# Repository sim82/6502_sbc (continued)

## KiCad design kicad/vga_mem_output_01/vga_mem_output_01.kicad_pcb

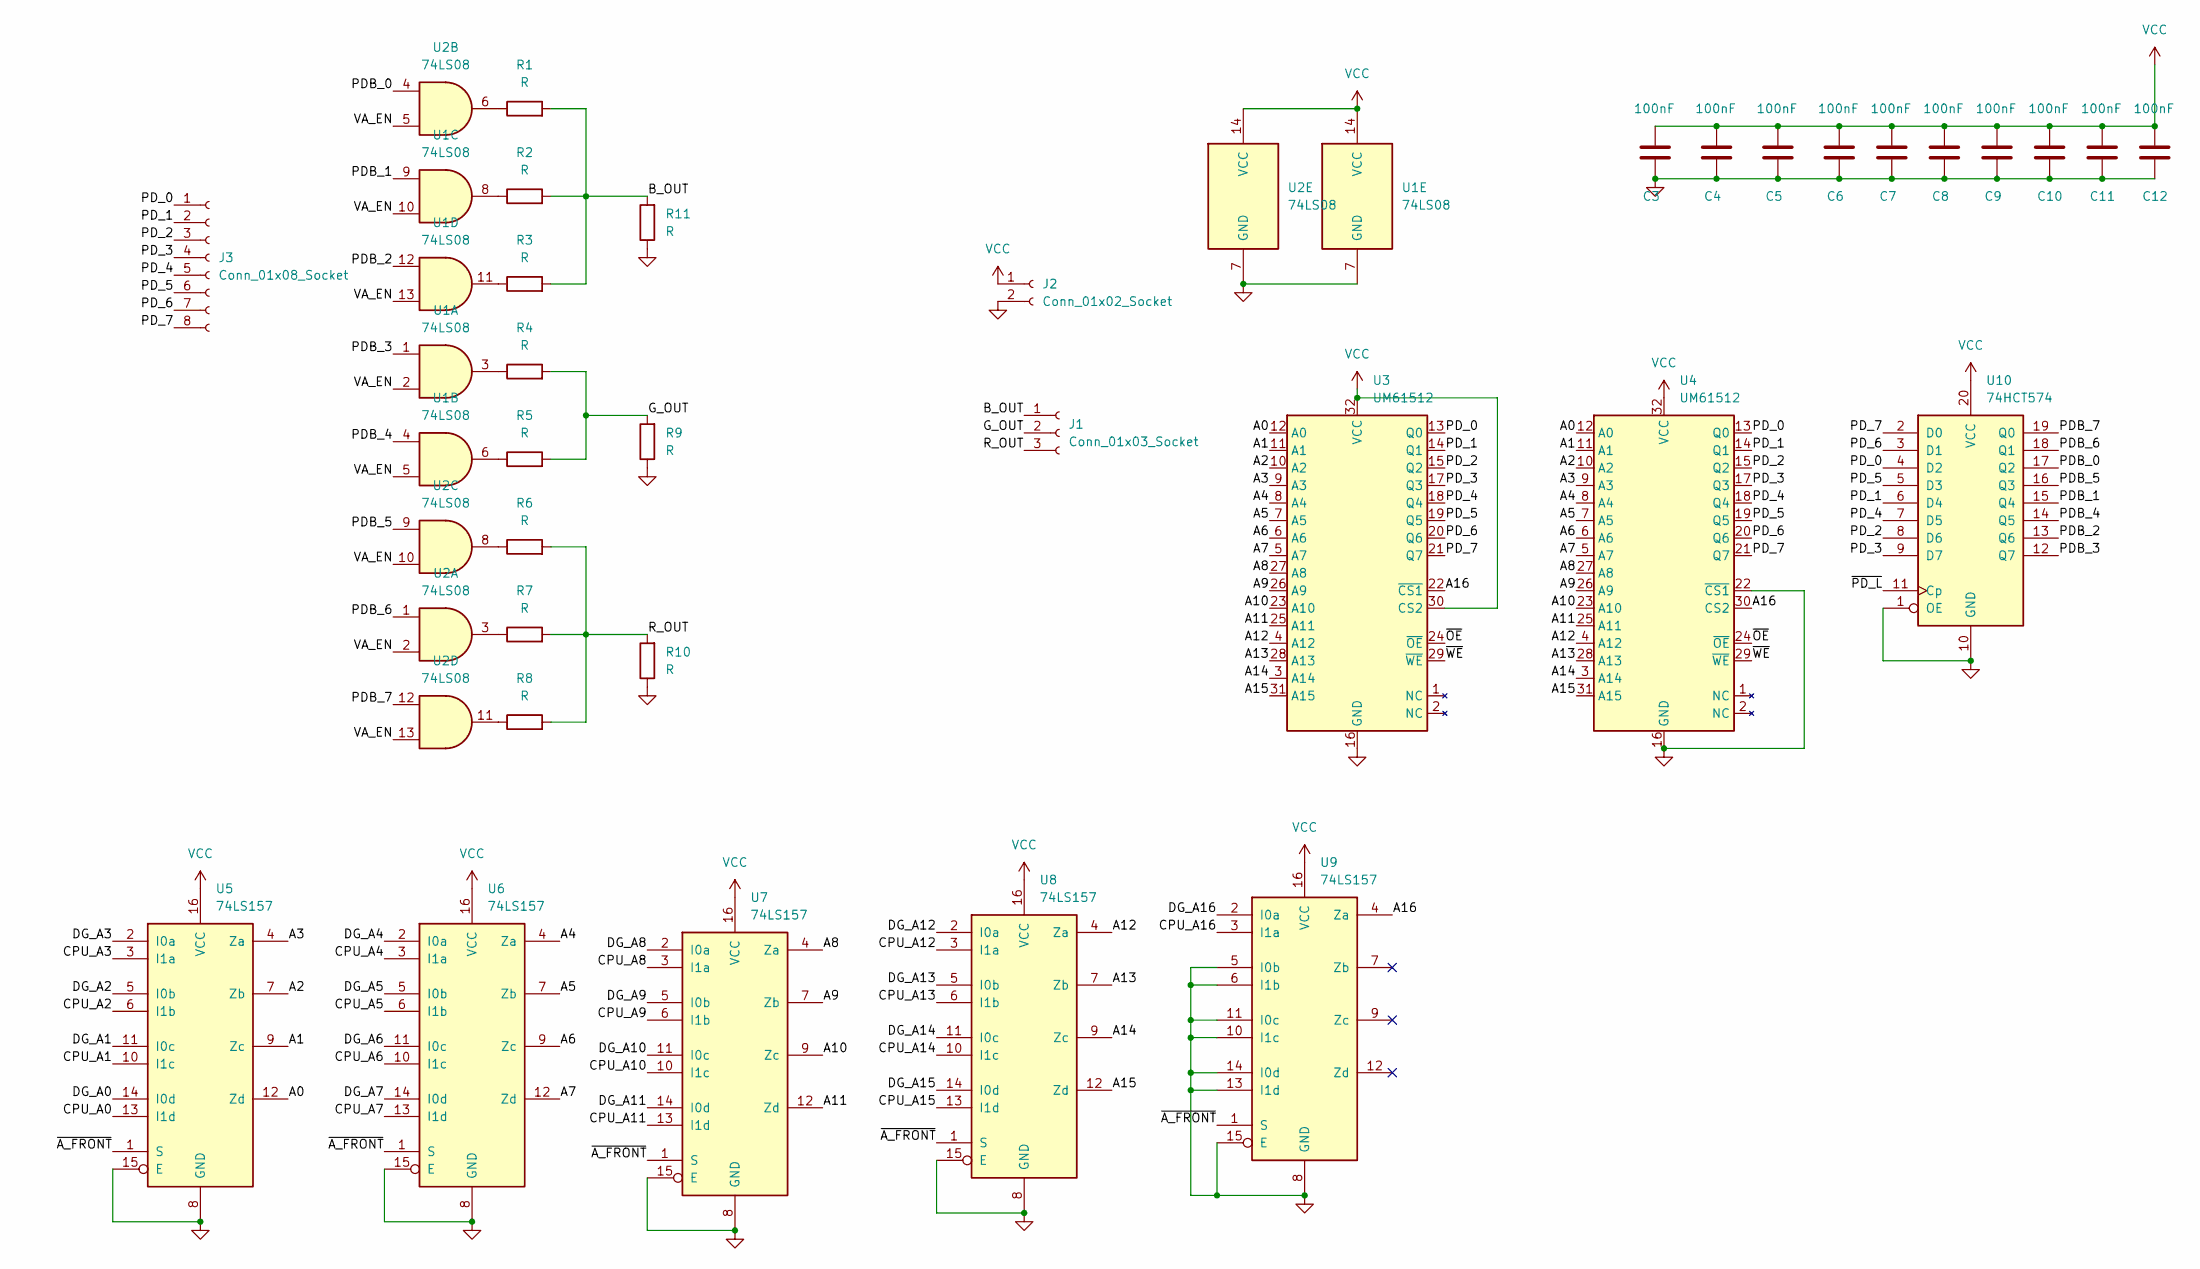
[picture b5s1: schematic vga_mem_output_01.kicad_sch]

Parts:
C3, C4, C5, C6, C7, C8, C9, C10, C11, C12: 100nF; C_0805_2012Metric_Pad1.18x1.45mm_HandSolder
J1: Conn_01x03_Socket; PinSocket_1x03_P2.54mm_Vertical
J2: Conn_01x02_Socket; PinSocket_1x02_P2.54mm_Vertical
J3: Conn_01x08_Socket; PinSocket_1x08_P2.54mm_Vertical
R1, R2, R3, R4, R5, R6, R7, R8, R9, R10, R11: R; R_Axial_DIN0204_L3.6mm_D1.6mm_P7.62mm_Horizontal
U1, U2: 74LS08; SO-14_3.9x8.65mm_P1.27mm
U3, U4: UM61512; DIP-32_W7.62mm
U5, U6, U7, U8, U9: 74LS157; SO-16_3.9x9.9mm_P1.27mm
U10: 74HCT574; SO-20_5.3x12.6mm_P1.27mm

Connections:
/A0: U3.12 (A0), U4.12 (A0), U5.12 (Zd)
/A1: U3.11 (A1), U4.11 (A1), U5.9 (Zc)
/A2: U3.10 (A2), U4.10 (A2), U5.7 (Zb)
/A3: U3.9 (A3), U4.9 (A3), U5.4 (Za)
/A4: U3.8 (A4), U4.8 (A4), U6.4 (Za)
/A5: U3.7 (A5), U4.7 (A5), U6.7 (Zb)
/A6: U3.6 (A6), U4.6 (A6), U6.9 (Zc)
/A7: U3.5 (A7), U4.5 (A7), U6.12 (Zd)
/A8: U3.27 (A8), U4.27 (A8), U7.4 (Za)
/A9: U3.26 (A9), U4.26 (A9), U7.7 (Zb)
/A10: U3.23 (A10), U4.23 (A10), U7.9 (Zc)
/A11: U3.25 (A11), U4.25 (A11), U7.12 (Zd)
/A12: U3.4 (A12), U4.4 (A12), U8.4 (Za)
/A13: U3.28 (A13), U4.28 (A13), U8.7 (Zb)
/A14: U3.3 (A14), U4.3 (A14), U8.9 (Zc)
/A15: U3.31 (A15), U4.31 (A15), U8.12 (Zd)
/A16: U3.22 (~CS1), U4.30 (CS2), U9.4 (Za)
/B_OUT: J1.1, R1.2, R2.2, R3.2, R11.2
/CPU_A0: U5.13 (I1d)
/CPU_A1: U5.10 (I1c)
/CPU_A2: U5.6 (I1b)
/CPU_A3: U5.3 (I1a)
/CPU_A4: U6.3 (I1a)
/CPU_A5: U6.6 (I1b)
/CPU_A6: U6.10 (I1c)
/CPU_A7: U6.13 (I1d)
/CPU_A8: U7.3 (I1a)
/CPU_A9: U7.6 (I1b)
/CPU_A10: U7.10 (I1c)
/CPU_A11: U7.13 (I1d)
/CPU_A12: U8.3 (I1a)
/CPU_A13: U8.6 (I1b)
/CPU_A14: U8.10 (I1c)
/CPU_A15: U8.13 (I1d)
/CPU_A16: U9.3 (I1a)
/DG_A0: U5.14 (I0d)
/DG_A1: U5.11 (I0c)
/DG_A2: U5.5 (I0b)
/DG_A3: U5.2 (I0a)
/DG_A4: U6.2 (I0a)
/DG_A5: U6.5 (I0b)
/DG_A6: U6.11 (I0c)
/DG_A7: U6.14 (I0d)
/DG_A8: U7.2 (I0a)
/DG_A9: U7.5 (I0b)
/DG_A10: U7.11 (I0c)
/DG_A11: U7.14 (I0d)
/DG_A12: U8.2 (I0a)
/DG_A13: U8.5 (I0b)
/DG_A14: U8.11 (I0c)
/DG_A15: U8.14 (I0d)
/DG_A16: U9.2 (I0a)
/G_OUT: J1.2, R4.2, R5.2, R9.2
/PDB_0: U2.4, U10.17 (Q2)
/PDB_1: U1.9, U10.15 (Q4)
/PDB_2: U1.12, U10.13 (Q6)
/PDB_3: U1.1, U10.12 (Q7)
/PDB_4: U1.4, U10.14 (Q5)
/PDB_5: U2.9, U10.16 (Q3)
/PDB_6: U2.1, U10.18 (Q1)
/PDB_7: U2.12, U10.19 (Q0)
/PD_0: J3.1, U3.13 (Q0), U4.13 (Q0), U10.4 (D2)
/PD_1: J3.2, U3.14 (Q1), U4.14 (Q1), U10.6 (D4)
/PD_2: J3.3, U3.15 (Q2), U4.15 (Q2), U10.8 (D6)
/PD_3: J3.4, U3.17 (Q3), U4.17 (Q3), U10.9 (D7)
/PD_4: J3.5, U3.18 (Q4), U4.18 (Q4), U10.7 (D5)
/PD_5: J3.6, U3.19 (Q5), U4.19 (Q5), U10.5 (D3)
/PD_6: J3.7, U3.20 (Q6), U4.20 (Q6), U10.3 (D1)
/PD_7: J3.8, U3.21 (Q7), U4.21 (Q7), U10.2 (D0)
/R_OUT: J1.3, R6.2, R7.2, R8.2, R10.2
/VA_EN: U1.2, U1.5, U1.10, U1.13, U2.2, U2.5, U2.10, U2.13
/~A_FRONT: U5.1 (S), U6.1 (S), U7.1 (S), U8.1 (S), U9.1 (S)
/~OE: U3.24 (~OE), U4.24 (~OE)
/~PD_L: U10.11 (Cp)
/~WE: U3.29 (~WE), U4.29 (~WE)
GND: C3.2, C4.2, C5.2, C6.2, C7.2, C8.2, C9.2, C10.2, C11.2, C12.2, J2.2, R9.1, R10.1, R11.1, U1.7 (GND), U2.7 (GND), U3.16 (GND), U4.16 (GND), U4.22 (~CS1), U5.8 (GND), U5.15 (E), U6.8 (GND), U6.15 (E), U7.8 (GND), U7.15 (E), U8.8 (GND), U8.15 (E), U9.5 (I0b), U9.6 (I1b), U9.8 (GND), U9.10 (I1c), U9.11 (I0c), U9.13 (I1d), U9.14 (I0d), U9.15 (E), U10.1 (OE), U10.10 (GND)
unnamed: R1.1, U2.6
unnamed: R2.1, U1.8
unnamed: R3.1, U1.11
unnamed: R4.1, U1.3
unnamed: R5.1, U1.6
unnamed: R6.1, U2.8
unnamed: R7.1, U2.3
unnamed: R8.1, U2.11
VCC: C3.1, C4.1, C5.1, C6.1, C7.1, C8.1, C9.1, C10.1, C11.1, C12.1, J2.1, U1.14 (VCC), U2.14 (VCC), U3.30 (CS2), U3.32 (VCC), U4.32 (VCC), U5.16 (VCC), U6.16 (VCC), U7.16 (VCC), U8.16 (VCC), U9.16 (VCC), U10.20 (VCC)

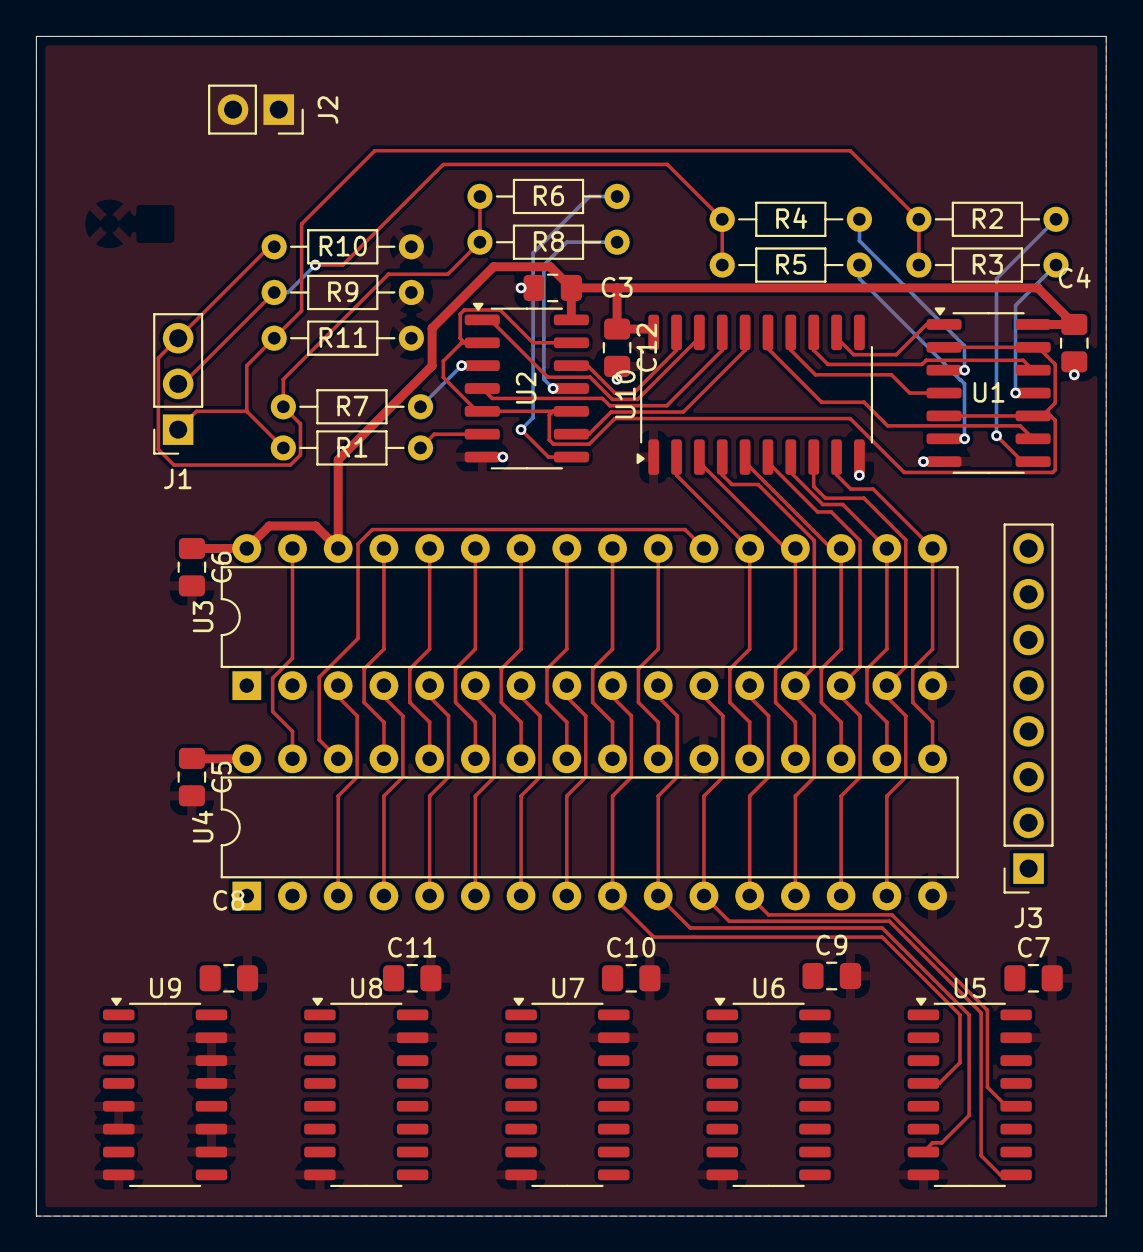
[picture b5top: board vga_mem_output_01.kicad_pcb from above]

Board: 2 copper layers, 59.4 x 65.5 mm, 34 parts (0 on the bottom side), 50 nets.

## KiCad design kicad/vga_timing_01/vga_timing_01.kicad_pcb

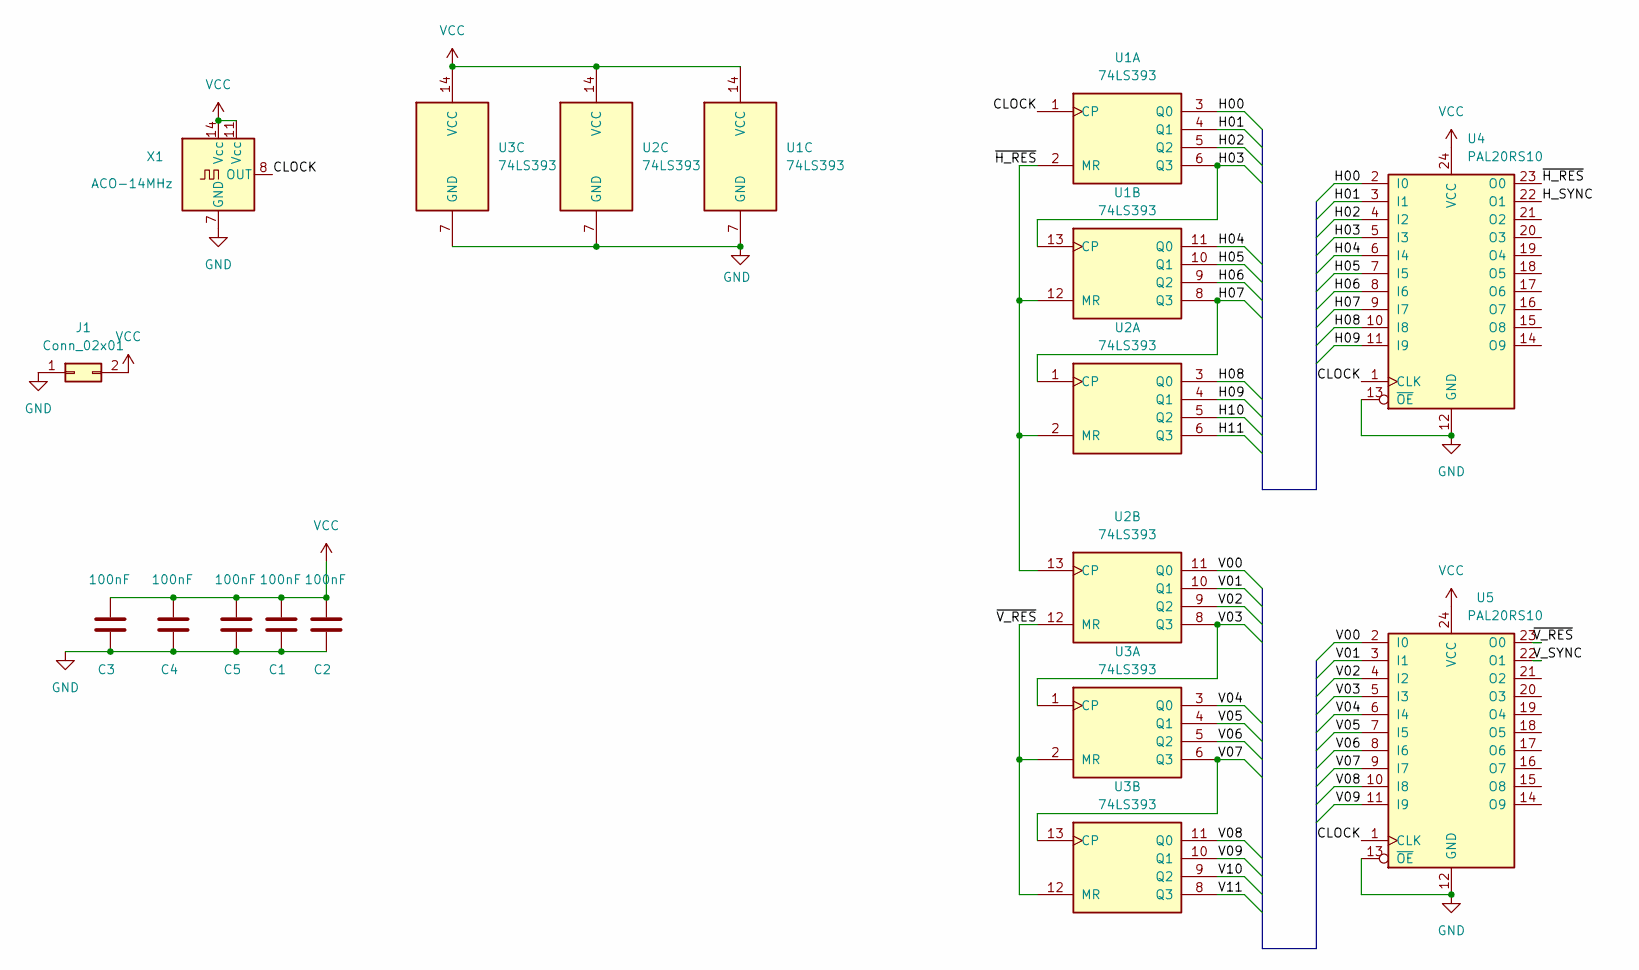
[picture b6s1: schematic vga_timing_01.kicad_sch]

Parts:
C1, C2, C3, C4, C5: 100nF; C_0805_2012Metric_Pad1.18x1.45mm_HandSolder
J1: Conn_02x01; PinSocket_2x01_P1.27mm_Vertical
U1, U2, U3: 74LS393; SO-14_3.9x8.65mm_P1.27mm
U4, U5: PAL20RS10; DIP-24_W7.62mm_Socket
X1: ACO-14MHz; DIP-14_W7.62mm_Socket

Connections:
/CLOCK: U1.1 (CP), U4.1 (CLK), U5.1 (CLK), X1.8 (OUT)
/H00: U1.3 (Q0), U4.2 (I0)
/H01: U1.4 (Q1), U4.3 (I1)
/H02: U1.5 (Q2), U4.4 (I2)
/H03: U1.6 (Q3), U1.13 (CP), U4.5 (I3)
/H04: U1.11 (Q0), U4.6 (I4)
/H05: U1.10 (Q1), U4.7 (I5)
/H06: U1.9 (Q2), U4.8 (I6)
/H07: U1.8 (Q3), U2.1 (CP), U4.9 (I7)
/H08: U2.3 (Q0), U4.10 (I8)
/H09: U2.4 (Q1), U4.11 (I9)
/H10: U2.5 (Q2)
/H11: U2.6 (Q3)
/H_SYNC: U4.22 (O1)
/V00: U2.11 (Q0), U5.2 (I0)
/V01: U2.10 (Q1), U5.3 (I1)
/V02: U2.9 (Q2), U5.4 (I2)
/V03: U2.8 (Q3), U3.1 (CP), U5.5 (I3)
/V04: U3.3 (Q0), U5.6 (I4)
/V05: U3.4 (Q1), U5.7 (I5)
/V06: U3.5 (Q2), U5.8 (I6)
/V07: U3.6 (Q3), U3.13 (CP), U5.9 (I7)
/V08: U3.11 (Q0), U5.10 (I8)
/V09: U3.10 (Q1), U5.11 (I9)
/V10: U3.9 (Q2)
/V11: U3.8 (Q3)
/V_SYNC: U5.22 (O1)
/~H_RES: U1.2 (MR), U1.12 (MR), U2.2 (MR), U2.13 (CP), U4.23 (O0)
/~V_RES: U2.12 (MR), U3.2 (MR), U3.12 (MR), U5.23 (O0)
GND: C1.2, C2.2, C3.2, C4.2, C5.2, J1.1, U1.7 (GND), U2.7 (GND), U3.7 (GND), U4.12 (GND), U4.13 (~OE), U5.12 (GND), U5.13 (~OE), X1.7 (GND)
VCC: C1.1, C2.1, C3.1, C4.1, C5.1, J1.2, U1.14 (VCC), U2.14 (VCC), U3.14 (VCC), U4.24 (VCC), U5.24 (VCC), X1.11 (Vcc), X1.14 (Vcc)

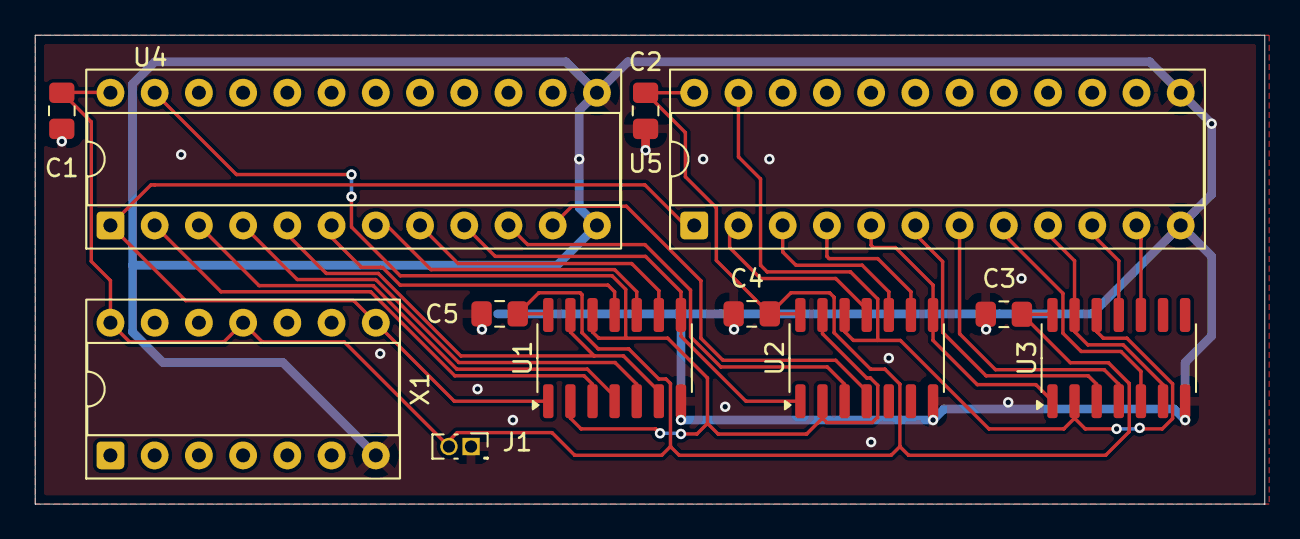
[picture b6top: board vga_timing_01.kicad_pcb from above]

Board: 2 copper layers, 70.6 x 26.9 mm, 12 parts (0 on the bottom side), 25 nets.

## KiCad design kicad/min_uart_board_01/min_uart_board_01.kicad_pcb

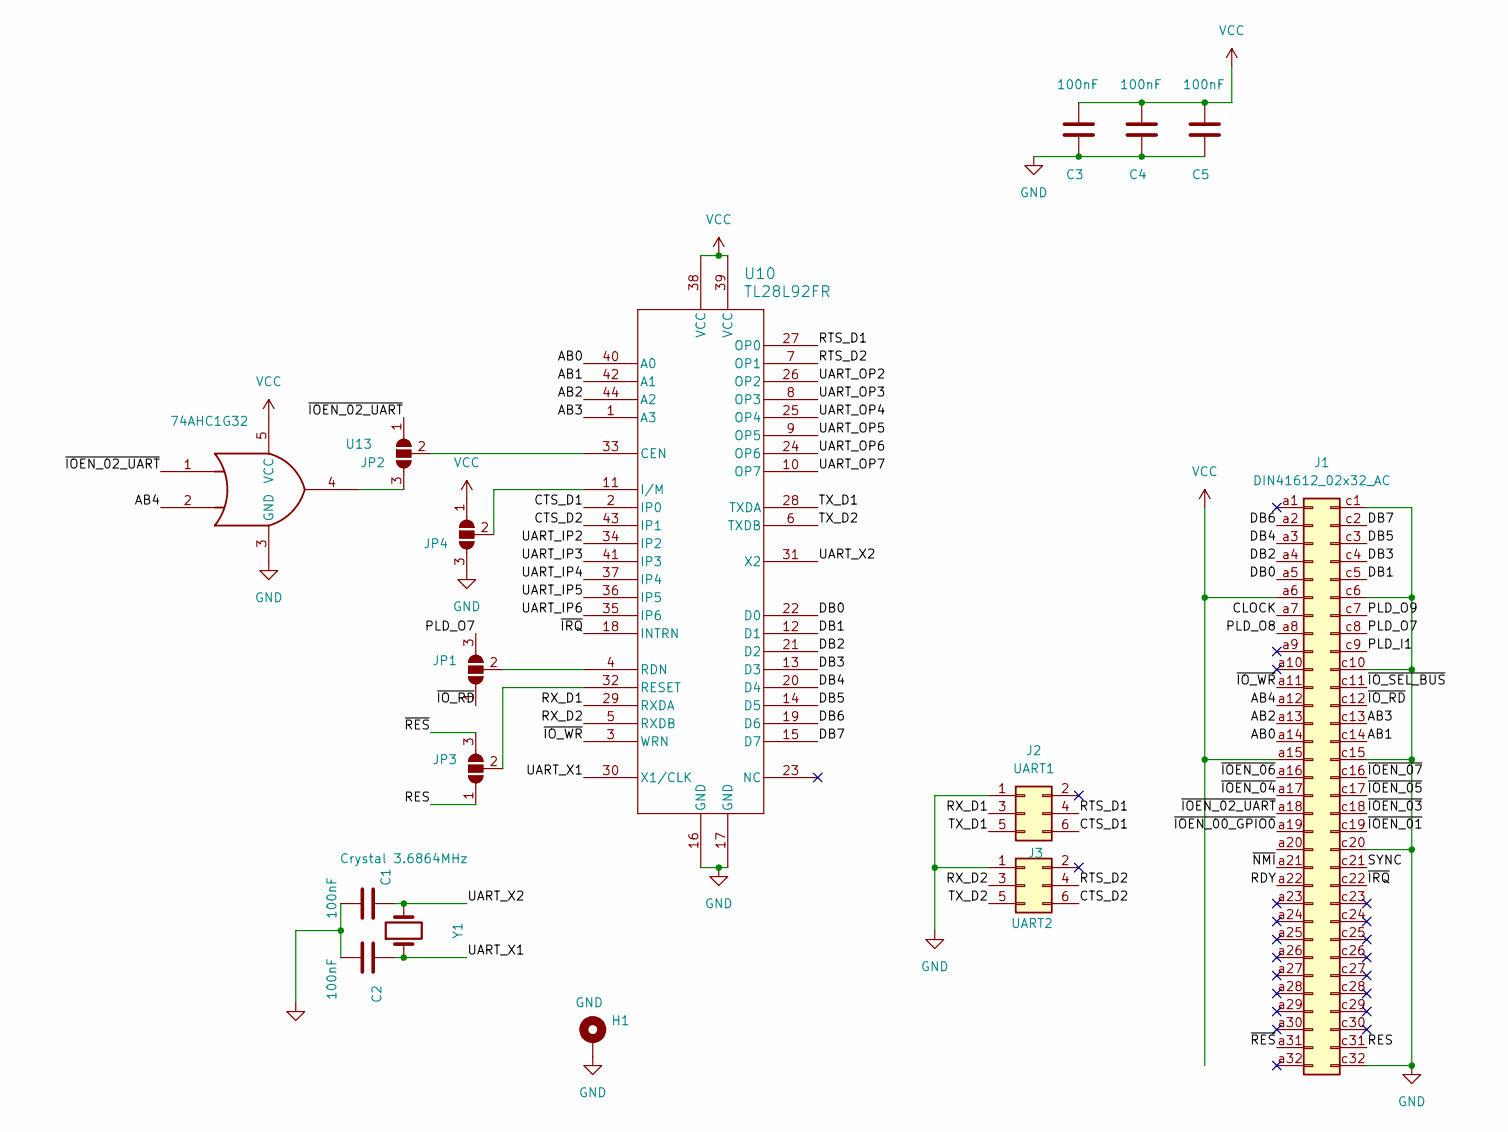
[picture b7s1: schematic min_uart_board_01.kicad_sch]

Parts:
C1, C2: 100nF; C_Disc_D4.7mm_W2.5mm_P5.00mm
C3, C4, C5: 100nF; C_0805_2012Metric_Pad1.18x1.45mm_HandSolder
H1: GND; MountingHole_3.2mm_M3_DIN965_Pad
J1: DIN41612_02x32_AC; DIN41612_C_2x32_Male_Horizontal_THT
J2: UART1; PinHeader_2x03_P2.54mm_Horizontal
J3: UART2; PinHeader_2x03_P2.54mm_Horizontal
JP1, JP2, JP3, JP4: SolderJumper_3_Open; SolderJumper-3_P1.3mm_Open_RoundedPad1.0x1.5mm
U10: TL28L92FR; MQFP-44_10x10mm_P0.8mm
U13: 74AHC1G32; SOT-23-5_HandSoldering
Y1: Crystal 3.6864MHz; Crystal_HC49-4H_Vertical

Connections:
/AB0: J1.a14, U10.40 (A0)
/AB1: J1.c14, U10.42 (A1)
/AB2: J1.a13, U10.44 (A2)
/AB3: J1.c13, U10.1 (A3)
/AB4: J1.a12, U13.2
/CLOCK: J1.a7
/CTS_D1: J2.6, U10.2 (IP0)
/CTS_D2: J3.6, U10.43 (IP1)
/DB0: J1.a5, U10.22 (D0)
/DB1: J1.c5, U10.12 (D1)
/DB2: J1.a4, U10.21 (D2)
/DB3: J1.c4, U10.13 (D3)
/DB4: J1.a3, U10.20 (D4)
/DB5: J1.c3, U10.14 (D5)
/DB6: J1.a2, U10.19 (D6)
/DB7: J1.c2, U10.15 (D7)
/PLD_I1: J1.c9
/PLD_O7: J1.c8, JP1.3 (B)
/PLD_O8: J1.a8
/PLD_O9: J1.c7
/RDY: J1.a22
/RES: J1.c31, JP3.1 (A)
/RTS_D1: J2.4, U10.27 (OP0)
/RTS_D2: J3.4, U10.7 (OP1)
/RX_D1: J2.3, U10.29 (RXDA)
/RX_D2: J3.3, U10.5 (RXDB)
/SYNC: J1.c21
/TX_D1: J2.5, U10.28 (TXDA)
/TX_D2: J3.5, U10.6 (TXDB)
/UART_IP2: U10.34 (IP2)
/UART_IP3: U10.41 (IP3)
/UART_IP4: U10.37 (IP4)
/UART_IP5: U10.36 (IP5)
/UART_IP6: U10.35 (IP6)
/UART_OP2: U10.26 (OP2)
/UART_OP3: U10.8 (OP3)
/UART_OP4: U10.25 (OP4)
/UART_OP5: U10.9 (OP5)
/UART_OP6: U10.24 (OP6)
/UART_OP7: U10.10 (OP7)
/UART_X1: C2.1, U10.30 (X1/CLK), Y1.1
/UART_X2: C1.1, U10.31 (X2), Y1.2
/~IOEN_00_GPIO0: J1.a19
/~IOEN_01: J1.c19
/~IOEN_02_UART: J1.a18, JP2.1 (A), U13.1
/~IOEN_03: J1.c18
/~IOEN_04: J1.a17
/~IOEN_05: J1.c17
/~IOEN_06: J1.a16
/~IOEN_07: J1.c16
/~IO_RD: J1.c12, JP1.1 (A)
/~IO_SEL_BUS: J1.c11
/~IO_WR: J1.a11, U10.3 (WRN)
/~IRQ: J1.c22, U10.18 (INTRN)
/~NMI: J1.a21
/~RES: J1.a31, JP3.3 (B)
GND: C1.2, C2.2, C3.2, C4.2, C5.2, H1.1, J1.c1, J1.c6, J1.c10, J1.c15, J1.c20, J1.c32, J2.1, J3.1, JP4.3 (B), U10.16 (GND), U10.17 (GND), U13.3 (GND)
unnamed: JP1.2 (C), U10.4 (RDN)
unnamed: JP2.3 (B), U13.4
unnamed: JP2.2 (C), U10.33 (CEN)
unnamed: JP3.2 (C), U10.32 (RESET)
unnamed: JP4.2 (C), U10.11 (I/M)
VCC: C3.1, C4.1, C5.1, J1.a6, J1.a15, JP4.1 (A), U10.38 (VCC), U10.39 (VCC), U13.5 (VCC)

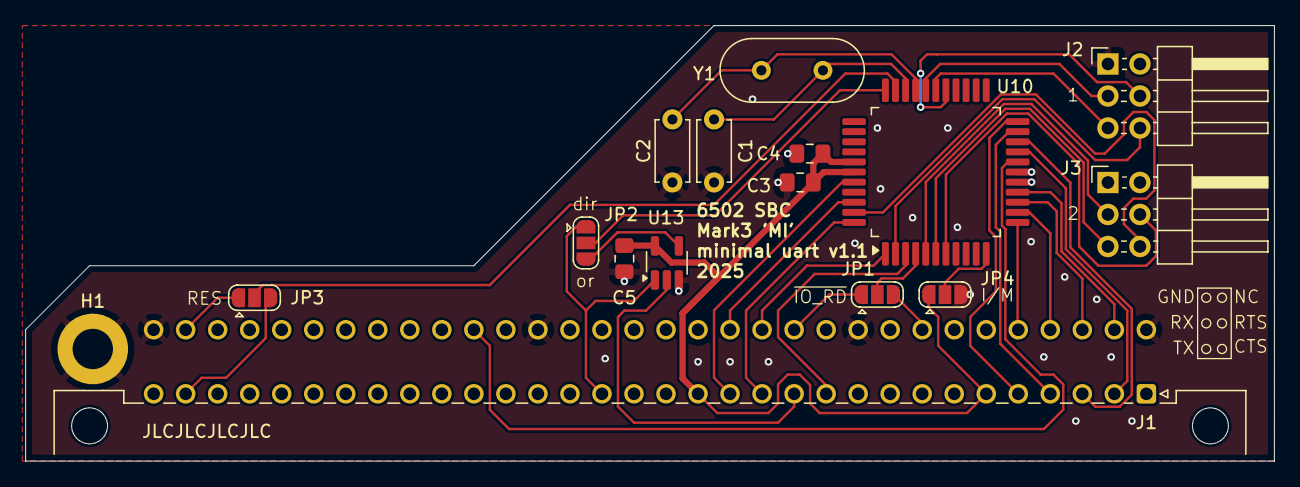
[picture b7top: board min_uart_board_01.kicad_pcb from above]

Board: 2 copper layers, 99.1 x 34.5 mm, 16 parts (0 on the bottom side), 37 nets.

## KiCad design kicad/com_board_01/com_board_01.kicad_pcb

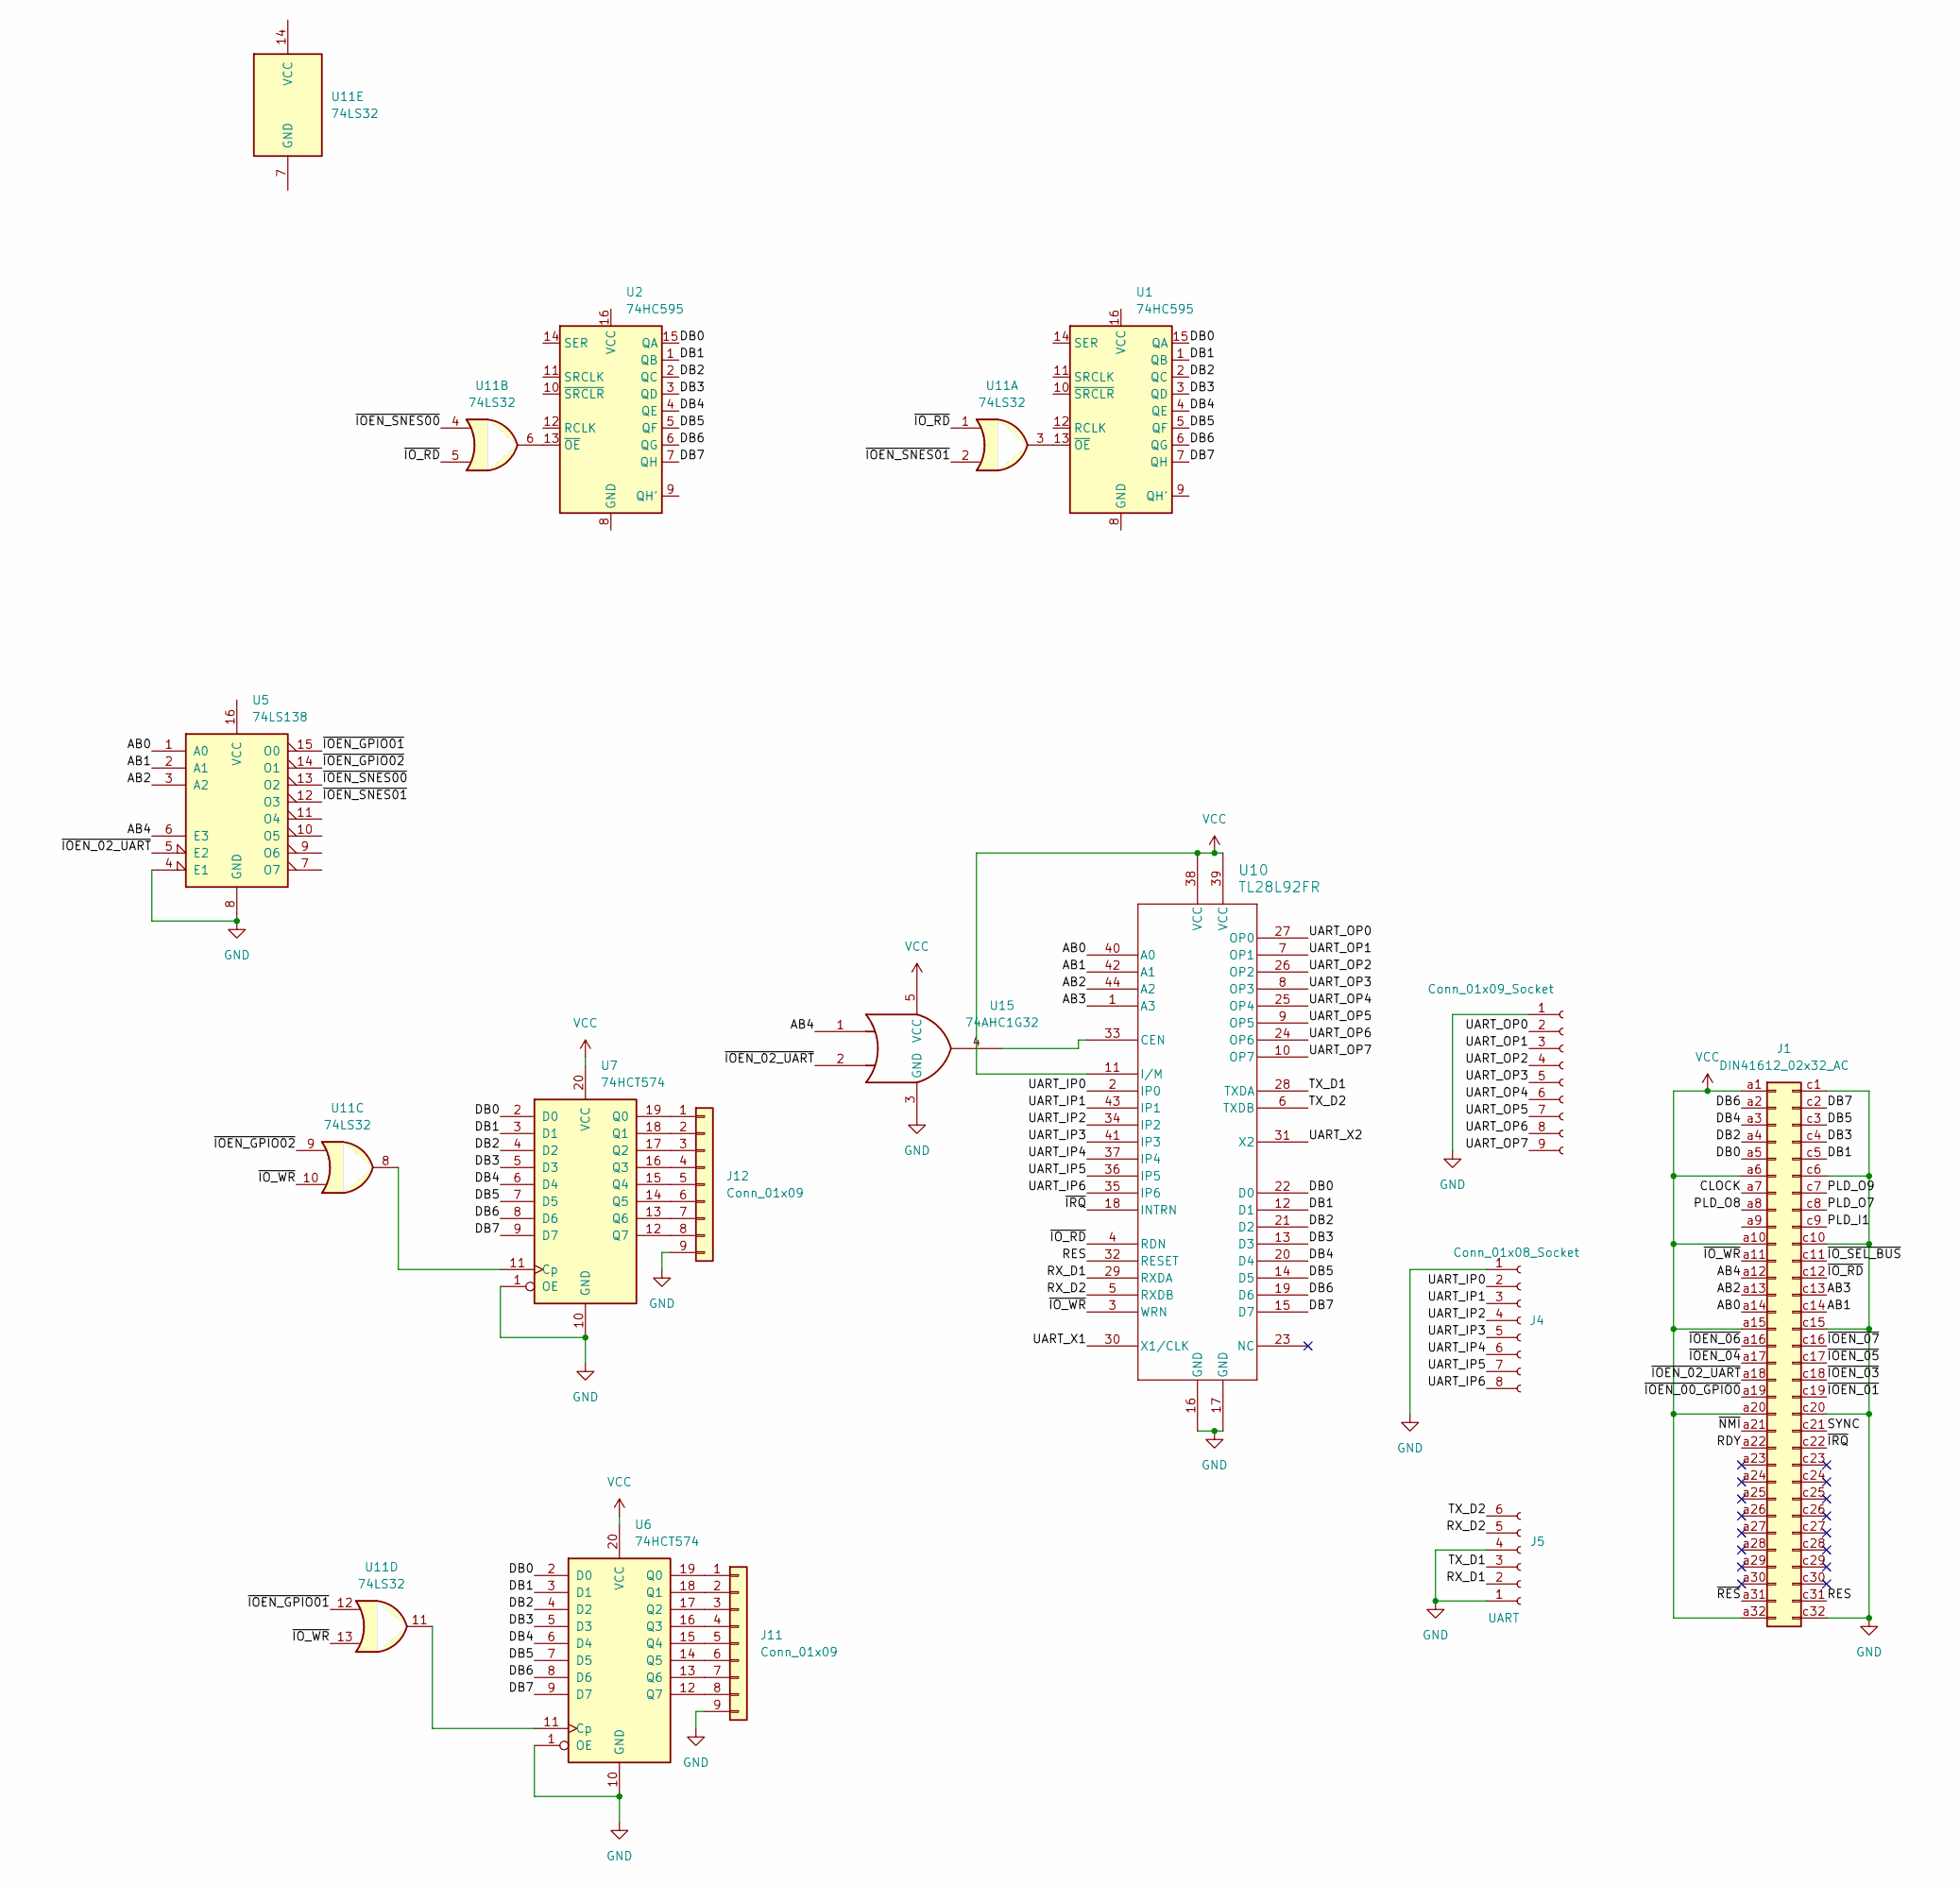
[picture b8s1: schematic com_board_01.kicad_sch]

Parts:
J1: DIN41612_02x32_AC; DIN41612_C_2x32_Male_Horizontal_THT
J3: Conn_01x09_Socket; PinSocket_1x09_P2.54mm_Vertical
J4: Conn_01x08_Socket; PinSocket_1x08_P2.54mm_Vertical
J5: UART; PinSocket_1x06_P2.54mm_Vertical
J11, J12: Conn_01x09; PinSocket_1x09_P2.54mm_Vertical
U1, U2: 74HC595; SOIC-16_3.9x9.9mm_P1.27mm
U5: 74LS138; SO-16_3.9x9.9mm_P1.27mm
U6, U7: 74HCT574; SO-20_12.8x7.5mm_P1.27mm
U10: TL28L92FR; MQFP-44_10x10mm_P0.8mm
U11: 74LS32; SO-14_3.9x8.65mm_P1.27mm
U15: 74AHC1G32; SOT-23-5_HandSoldering

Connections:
/AB0: J1.a14, U5.1 (A0), U10.40 (A0)
/AB1: J1.c14, U5.2 (A1), U10.42 (A1)
/AB2: J1.a13, U5.3 (A2), U10.44 (A2)
/AB3: J1.c13, U10.1 (A3)
/AB4: J1.a12, U5.6 (E3), U15.1
/CLOCK: J1.a7
/DB0: J1.a5, U1.15 (QA), U2.15 (QA), U6.2 (D0), U7.2 (D0), U10.22 (D0)
/DB1: J1.c5, U1.1 (QB), U2.1 (QB), U6.3 (D1), U7.3 (D1), U10.12 (D1)
/DB2: J1.a4, U1.2 (QC), U2.2 (QC), U6.4 (D2), U7.4 (D2), U10.21 (D2)
/DB3: J1.c4, U1.3 (QD), U2.3 (QD), U6.5 (D3), U7.5 (D3), U10.13 (D3)
/DB4: J1.a3, U1.4 (QE), U2.4 (QE), U6.6 (D4), U7.6 (D4), U10.20 (D4)
/DB5: J1.c3, U1.5 (QF), U2.5 (QF), U6.7 (D5), U7.7 (D5), U10.14 (D5)
/DB6: J1.a2, U1.6 (QG), U2.6 (QG), U6.8 (D6), U7.8 (D6), U10.19 (D6)
/DB7: J1.c2, U1.7 (QH), U2.7 (QH), U6.9 (D7), U7.9 (D7), U10.15 (D7)
/PLD_I1: J1.c9
/PLD_O7: J1.c8
/PLD_O8: J1.a8
/PLD_O9: J1.c7
/RDY: J1.a22
/RES: J1.c31, U10.32 (RESET)
/RX_D1: J5.2, U10.29 (RXDA)
/RX_D2: J5.5, U10.5 (RXDB)
/SYNC: J1.c21
/TX_D1: J5.3, U10.28 (TXDA)
/TX_D2: J5.6, U10.6 (TXDB)
/UART_IP0: J4.2, U10.2 (IP0)
/UART_IP1: J4.3, U10.43 (IP1)
/UART_IP2: J4.4, U10.34 (IP2)
/UART_IP3: J4.5, U10.41 (IP3)
/UART_IP4: J4.6, U10.37 (IP4)
/UART_IP5: J4.7, U10.36 (IP5)
/UART_IP6: J4.8, U10.35 (IP6)
/UART_OP0: J3.2, U10.27 (OP0)
/UART_OP1: J3.3, U10.7 (OP1)
/UART_OP2: J3.4, U10.26 (OP2)
/UART_OP3: J3.5, U10.8 (OP3)
/UART_OP4: J3.6, U10.25 (OP4)
/UART_OP5: J3.7, U10.9 (OP5)
/UART_OP6: J3.8, U10.24 (OP6)
/UART_OP7: J3.9, U10.10 (OP7)
/UART_X1: U10.30 (X1/CLK)
/UART_X2: U10.31 (X2)
/~IOEN_00_GPIO0: J1.a19
/~IOEN_01: J1.c19
/~IOEN_02_UART: J1.a18, U5.5 (E2), U15.2
/~IOEN_03: J1.c18
/~IOEN_04: J1.a17
/~IOEN_05: J1.c17
/~IOEN_06: J1.a16
/~IOEN_07: J1.c16
/~IOEN_GPIO01: U5.15 (O0), U11.12
/~IOEN_GPIO02: U5.14 (O1), U11.9
/~IOEN_SNES00: U5.13 (O2), U11.4
/~IOEN_SNES01: U5.12 (O3), U11.2
/~IO_RD: J1.c12, U10.4 (RDN), U11.1, U11.5
/~IO_SEL_BUS: J1.c11
/~IO_WR: J1.a11, U10.3 (WRN), U11.10, U11.13
/~IRQ: J1.c22, U10.18 (INTRN)
/~NMI: J1.a21
/~RES: J1.a31
GND: J1.c1, J1.c6, J1.c10, J1.c15, J1.c20, J1.c32, J3.1, J4.1, J5.1, J5.4, J11.9, J12.9, U5.4 (E1), U5.8 (GND), U6.1 (OE), U6.10 (GND), U7.1 (OE), U7.10 (GND), U10.16 (GND), U10.17 (GND), U15.3 (GND)
unnamed: J11.1, U6.19 (Q0)
unnamed: J11.2, U6.18 (Q1)
unnamed: J11.3, U6.17 (Q2)
unnamed: J11.4, U6.16 (Q3)
unnamed: J11.5, U6.15 (Q4)
unnamed: J11.6, U6.14 (Q5)
unnamed: J11.7, U6.13 (Q6)
unnamed: J11.8, U6.12 (Q7)
unnamed: J12.1, U7.19 (Q0)
unnamed: J12.2, U7.18 (Q1)
unnamed: J12.3, U7.17 (Q2)
unnamed: J12.4, U7.16 (Q3)
unnamed: J12.5, U7.15 (Q4)
unnamed: J12.6, U7.14 (Q5)
unnamed: J12.7, U7.13 (Q6)
unnamed: J12.8, U7.12 (Q7)
unnamed: U1.13 (~OE), U11.3
unnamed: U2.13 (~OE), U11.6
unnamed: U6.11 (Cp), U11.11
unnamed: U7.11 (Cp), U11.8
unnamed: U10.33 (CEN), U15.4
VCC: J1.a1, J1.a6, J1.a10, J1.a15, J1.a20, J1.a32, U6.20 (VCC), U7.20 (VCC), U10.11 (I/M), U10.38 (VCC), U10.39 (VCC), U15.5 (VCC)

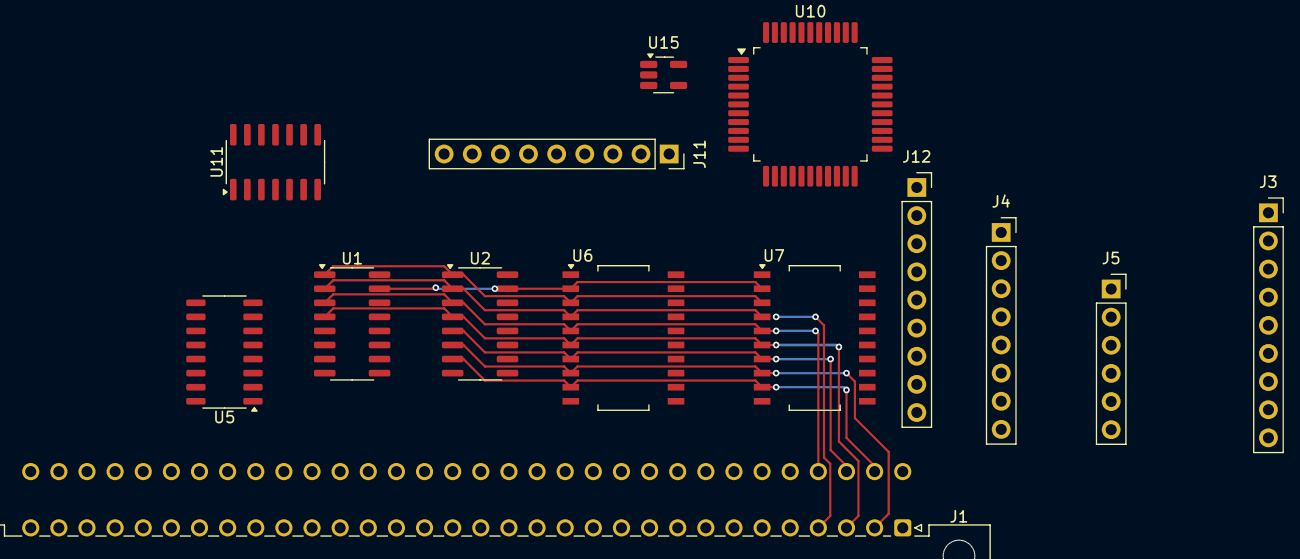
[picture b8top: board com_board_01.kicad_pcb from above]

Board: 2 copper layers, 14 parts (0 on the bottom side), 64 nets.
